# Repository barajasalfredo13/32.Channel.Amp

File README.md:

# 32.Channel.Amp
  
-----------------  
## Table of Contents
- 🔲 [Tile Boards]   
  - [Digi-Key Component List]
  - [Schematic]  
  - [Test Board]  
  - [Cell Board]  
- 🔲 [32 Cell Channel Receiver Board]  
  - [Cell Receiver Board]
  - [Cell Tester]
- 🔲 [Resources]  
  - [ Board Reference ]  
  - [ Amp Details ]  
  - [ Expected Connector ]  
  - [ Connections ]

----------------
## 🔲 ::: Tile Boards :::   
### : Component List :  
: Diodes :  
[ 1N4148W ](https://www.digikey.com/en/products/detail/smc-diode-solutions/1N4148W/6022450)  
[ BZT52H-A7V5-QX ](https://www.digikey.com/en/products/detail/nexperia-usa-inc/BZT52H-A7V5-QX/17295939)  
: Transistors :  
[ MMBT3904 ](https://www.digikey.com/en/products/detail/anbon-semiconductor-int-l-limited/MMBT3904/17284363)  
[ MMBT3906 ](https://www.digikey.com/en/products/detail/nte-electronics-inc/MMBT3906/11652283)  
: Capacitor :  
[ GRM188C81C106MA73J ](https://www.digikey.com/en/products/detail/murata-electronics/GRM188C81C106MA73J/4905316)  
: Resistors :  
[ RC0402JR-071KL ](https://www.digikey.com/en/products/detail/yageo/RC0402JR-071KL/726408)  
[ 311-4.7GRCT-ND ](https://www.digikey.com/en/products/detail/yageo/RC0603JR-074R7L/726784)  
: Cremat Holder :   
[ SMC-1-08-1-GT ](https://www.digikey.com/en/products/detail/adam-tech/SMC-1-08-1-GT/9830825)  
: DSUB Connector :  
[50 D-Sub](https://www.digikey.com/en/products/detail/harting/09665627811/4322749)  
[9 D-Sub](https://www.digikey.com/en/products/detail/te-connectivity-amp-connectors/2311765-1/7794751)  

### : Schematic :  

### :: Test Board ::  

### :: Cell Board ::  

-------------------
## 🔲 :: 32 Cell Channel Receiver Board ::

### : Cell Receiver Board :  

### : Cell Tester :  
Cell Tester allows for easy and quick cell testing.  

## 🔲 ::: Resources :::    
:: Board Referenced ::  
[CR-150-R5](https://www.cremat.com/CR-150-R5.pdf)  
  
:: Amp Details ::  
[CREMAT CR-11X](https://www.cremat.com/CR-110-R2.1.pdf)  
  
:: Expected Connector ::  
[IFDGG501056AX](https://www.lesker.com/feedthroughs/instrument-feedthroughs-mpdt-subd/part/ifdgg501056ax)  
  
### :: Connections ::  
###[SMC-1-08-1-GT](https://www.digikey.com/en/products/detail/adam-tech/SMC-1-08-1-GT/9830825)###  
: Drawing :  
  
: Generated Footprint :  

###[50 Position D-Sub Plug, Male Pins Connector](https://www.digikey.com/en/products/detail/harting/09665627811/4322749)###    
: Drawing :  
  
: Generated Footprint :

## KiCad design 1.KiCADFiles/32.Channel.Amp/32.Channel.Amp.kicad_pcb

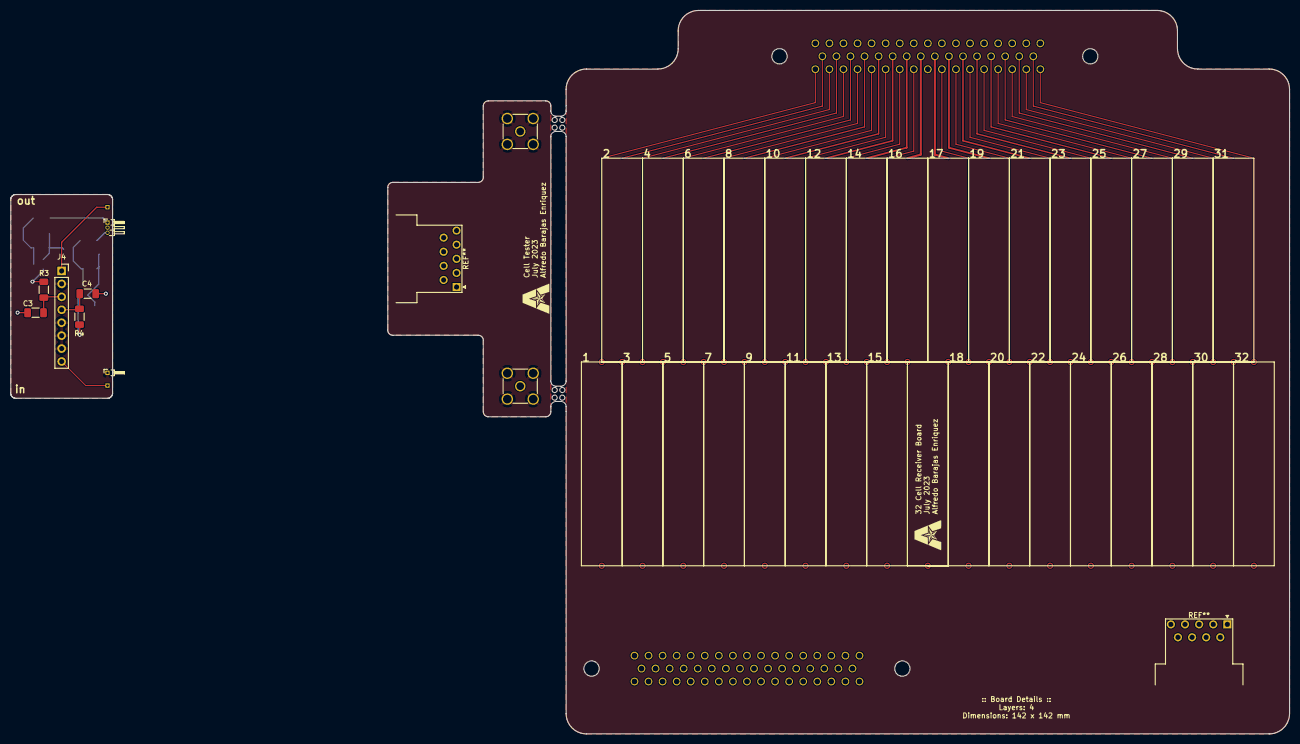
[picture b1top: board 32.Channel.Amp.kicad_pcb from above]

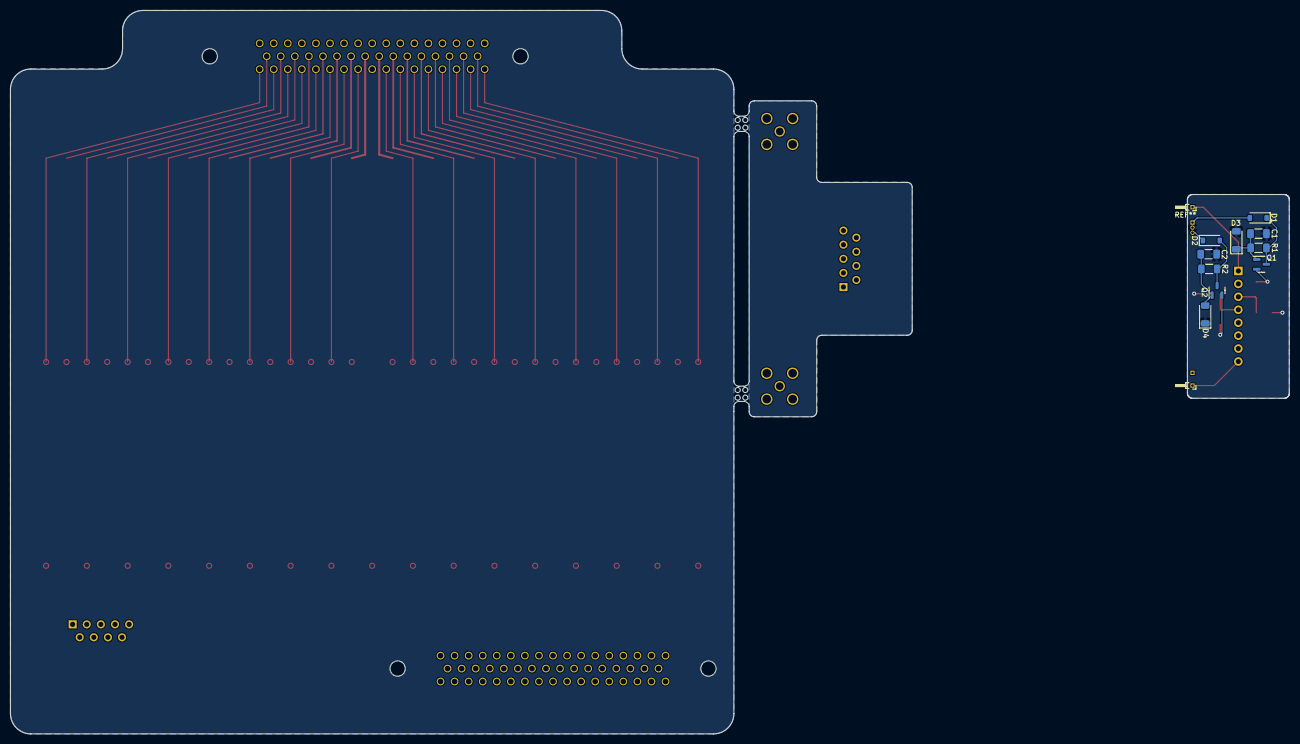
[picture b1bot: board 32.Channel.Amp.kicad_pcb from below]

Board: 4 copper layers, 251.0 x 142.0 mm, 17 parts (10 on the bottom side), 10 nets.

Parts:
C1, C2, C3, C4: 10uF; C_1206_3216Metric_Pad1.33x1.80mm_HandSolder
D1, D2: 1N4148W; D_SOD-123
D3, D4: BZV55B7V5; D_MiniMELF
J4: Conn_01x08; PinSocket_1x08_P2.54mm_Vertical
J5, J5#2: Conn_Coaxial_Out; SMA_Amphenol_901-144_Vertical
Q1: MMBT3904; SOT-23
Q2: MMBT3906; SOT-23
R1, R2: 1.0k; R_1206_3216Metric_Pad1.30x1.75mm_HandSolder
R3, R4: 4.7; R_1206_3216Metric_Pad1.30x1.75mm_HandSolder

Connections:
+11: D1.1 (K), Q1.3 (C), R1.1
-11: D2.2 (A), Q2.3 (C), R2.1
GND: C1.2, C2.2, C3.2, C4.2, D3.2 (A), D4.1 (K)
GND1: J4.2 (GND), J4.5, J4.6, J4.7, J5.2 (Ext), J5#2.2 (Ext)
unnamed: C1.1, D3.1 (K), Q1.1 (B), R1.2
unnamed: C2.1, D4.2 (A), Q2.1 (B), R2.2
unnamed: C3.1, J4.3, R3.2
unnamed: C4.1, J4.4, R4.2
unnamed: Q1.2 (E), R3.1
unnamed: Q2.2 (E), R4.1

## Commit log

2023-06-08 Created Template
2023-06-09 Added Skeleton Files
2023-06-09 Updated README for materials and references used
2023-06-09 Added DigiKey Items
2023-06-09 Minor Updates
2023-06-09 Created Footprints for Connector Components
2023-06-09 Updated Readme to Showcase Connectors
2023-06-10 Skeleton Layout Created
2023-06-12 Added DB9 and Created a General Layout
2023-06-13 Updated Files
2023-06-13 Added +V and -V regulators
2023-06-13 Added Power Regulator, RC Filtering, and 32 Channel
2023-06-20 Added Single Channel
2023-06-20 Small Adjustments to Single Channel
2023-06-20 Minor Changes
2023-06-20 Generated Gerber Files
2023-06-22 Updated Single Channel Test Board, Generated Gerber and Plot Files
2023-06-23 Updated Single Channel board as a Tile
2023-06-28 Template Format Created for 32 Channel Amp
2023-06-30 Created 16 Channel Box
2023-06-30 Updated Voltage Reference Points
2023-07-11 Updated 32 Channel Format, Included Chip Board
2023-07-11 Created two 32 Channel Boards. Adjusted traces for capacitance
2023-07-11 Uploaded Trace Width Calculator
2023-07-12 Added Amp Cell for 32 Channel Board
2023-07-12 Added Screenshots and Documentation Files
2023-07-12 Added Base Information to the ReadME file
2023-07-13 Updated Preview Files, Added Cell Pin Blueprint, Created Cell Tester
2023-07-13 Updated PCB Descriptions
2023-07-13 Cleaned Files
2023-07-14 Small Changes to Receiver Board
2023-07-14 Started signal trace lines
2023-07-16 Began adding signal traces, added cell holders
2023-07-16 Fixed cell board orientation, routed power lines, fixed wire capacitance with new lengths, updated excel sheet to include all traces
2023-07-17 Added all channel lenghts and widths
2023-07-17 Minor Fixes, Updated Excel Sheet to contain approx surface area
2023-07-17 Minor Graphic Changes
2023-07-17 Minor Adjustments
2023-07-17 Added Repository Link to Receiver Board
2023-07-21 Added 4/8/16 Layer boards
2023-07-23 Added board variants, minor fixes
2023-07-26 Started Sketch Designs with Multiple Layer Versions
2023-07-26 Added all tools in a separate folder
2023-07-30 Updated Receiver Board
2023-07-31 Added Base
2023-08-01 Mnimized Board Stack, Fixed Input Impedance
2023-08-02 Major Design Changes
2023-08-03 Minor file changes
2023-08-14 Updated schematic with new Zener Component, updated componenet list
2023-08-15 Added Tester Board
2023-08-15 Updated Readme Images
2024-05-20 Updated Schematic Diagram for Single Channel Board
